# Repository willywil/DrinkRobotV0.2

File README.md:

# DrinkRobotV0.2
Interrupt Test

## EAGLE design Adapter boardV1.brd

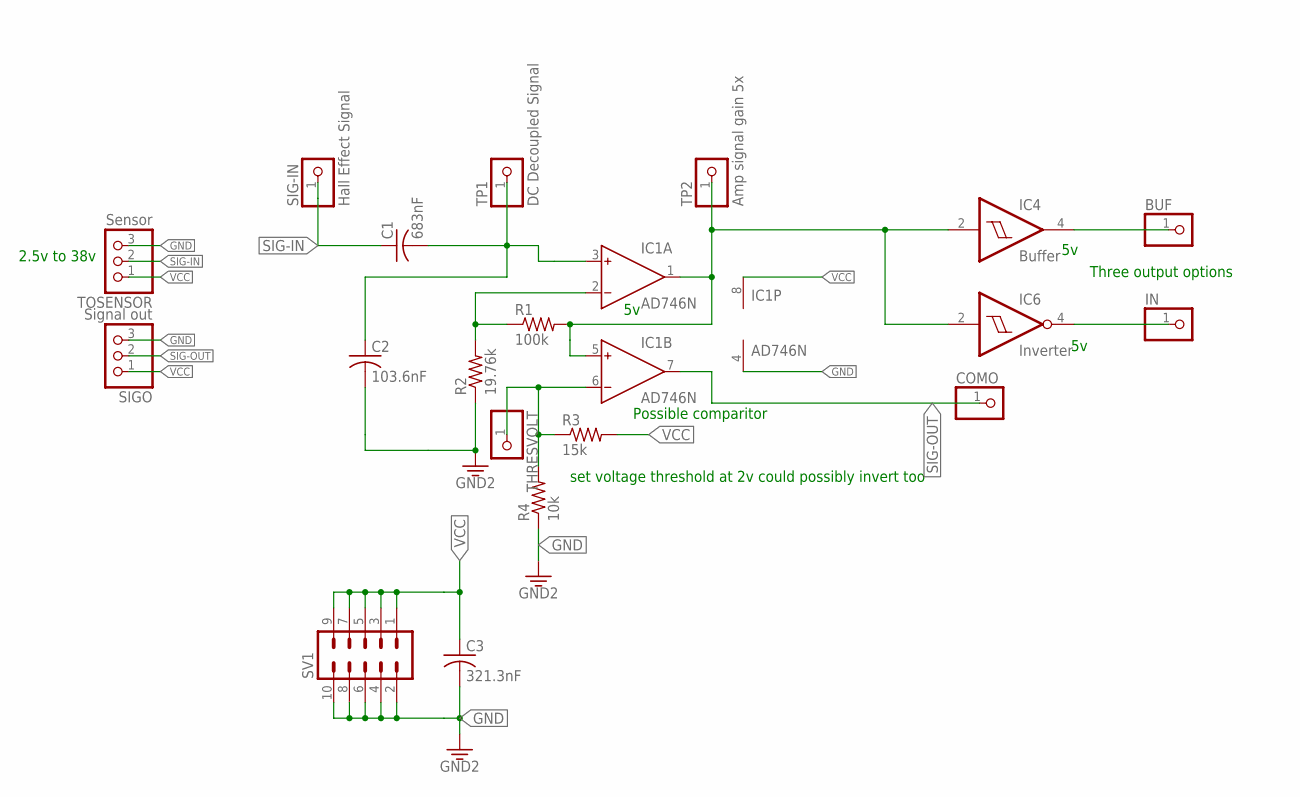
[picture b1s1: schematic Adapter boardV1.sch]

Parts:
BUF: PINHD-1X1; 1X01
C1: 683nF; C0805
C2: 103.6nF; C0805
C3: 321.3nF; C0805
COMO: PINHD-1X1; 1X01
IC1: AD746N; DIL08
IC4: Buffer; SOT23-5
IC6: Inverter; SOT23-5
IN: PINHD-1X1; 1X01
R1: 100k; 0805-THM-7
R2: 19.76k; 0805-THM-7
R3: 15k; 0805-THM-7
R4: 10k; 0805-THM-7
SIG-IN: Hall Effect Signal; 1X01
SIGO: Signal out; 1X03
SV1: MA05-2
THRESVOLT: PINHD-1X1; 1X01
TOSENSOR: Sensor; 1X03
TP1: DC Decoupled Signal; 1X01
TP2: Amp signal gain 5x; 1X01

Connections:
GND: C2.2, C3.2, IC1.4 (V-), IC4.3 (GND), IC6.3 (GND), R2.1, R4.1, SIGO.3, SV1.2, SV1.4, SV1.6, SV1.8, SV1.10, TOSENSOR.3
unnamed: C1.2, C2.1, IC1.3 (IN+), TP1.1
unnamed: IC1.6 (IN-), R3.1, R4.2, THRESVOLT.1
unnamed: BUF.1, IC4.4 (O)
unnamed: IC1.2 (IN-), R1.1, R2.2
unnamed: IC1.1 (OUT), IC1.5 (IN+), IC4.2 (I), IC6.2 (I), R1.2, TP2.1
unnamed: IC6.4 (O), IN.1
SIG-IN: C1.1, SIG-IN.1, TOSENSOR.2
SIG-OUT: COMO.1, IC1.7 (OUT), SIGO.2
VCC: C3.1, IC1.8 (V+), IC4.5 (VCC), IC6.5 (VCC), R3.2, SIGO.1, SV1.1, SV1.3, SV1.5, SV1.7, SV1.9, TOSENSOR.1

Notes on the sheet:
Possible comparitor
Three output options
set voltage threshold at 2v could possibly invert too
2.5v to 38v

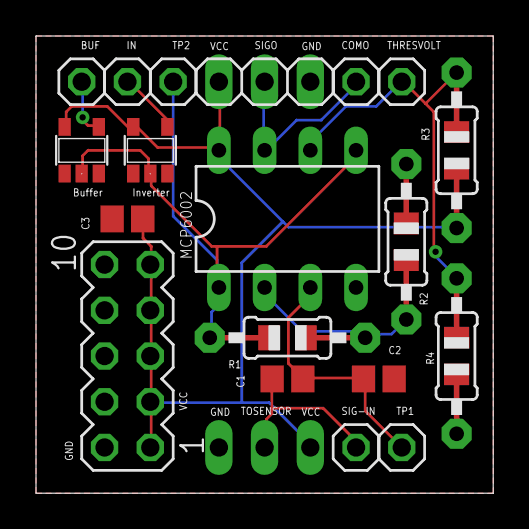
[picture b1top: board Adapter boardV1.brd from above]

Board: 2 copper layers, 25.4 x 25.4 mm, 20 parts (1 on the bottom side), 10 nets.

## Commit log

2018-08-05 Add .gitignore and .gitattributes.
2018-08-05 Add project files.
2018-08-06 interrupt test v0.2

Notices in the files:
parts and their libraries:
SparkFun-PowerSymbols: Licensing: Creative Commons ShareAlike 4.0 International - https://creativecommons.org/licenses/by-sa/4.0
